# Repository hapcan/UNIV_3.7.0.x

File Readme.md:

UNIV 3.7.0.x
============

BlIND CONTROLLER - 3 channel for AC motors 230V 200VA for DIN rail

Device webpage: http://hapcan.com/devices/universal/univ_3/univ_3-7-0-x/

Hardware created in Eagle PCB Software http://www.cadsoftusa.com/

Firmware created in Microchip MPLAB http://www.microchip.com/mplabide/ in assembly language

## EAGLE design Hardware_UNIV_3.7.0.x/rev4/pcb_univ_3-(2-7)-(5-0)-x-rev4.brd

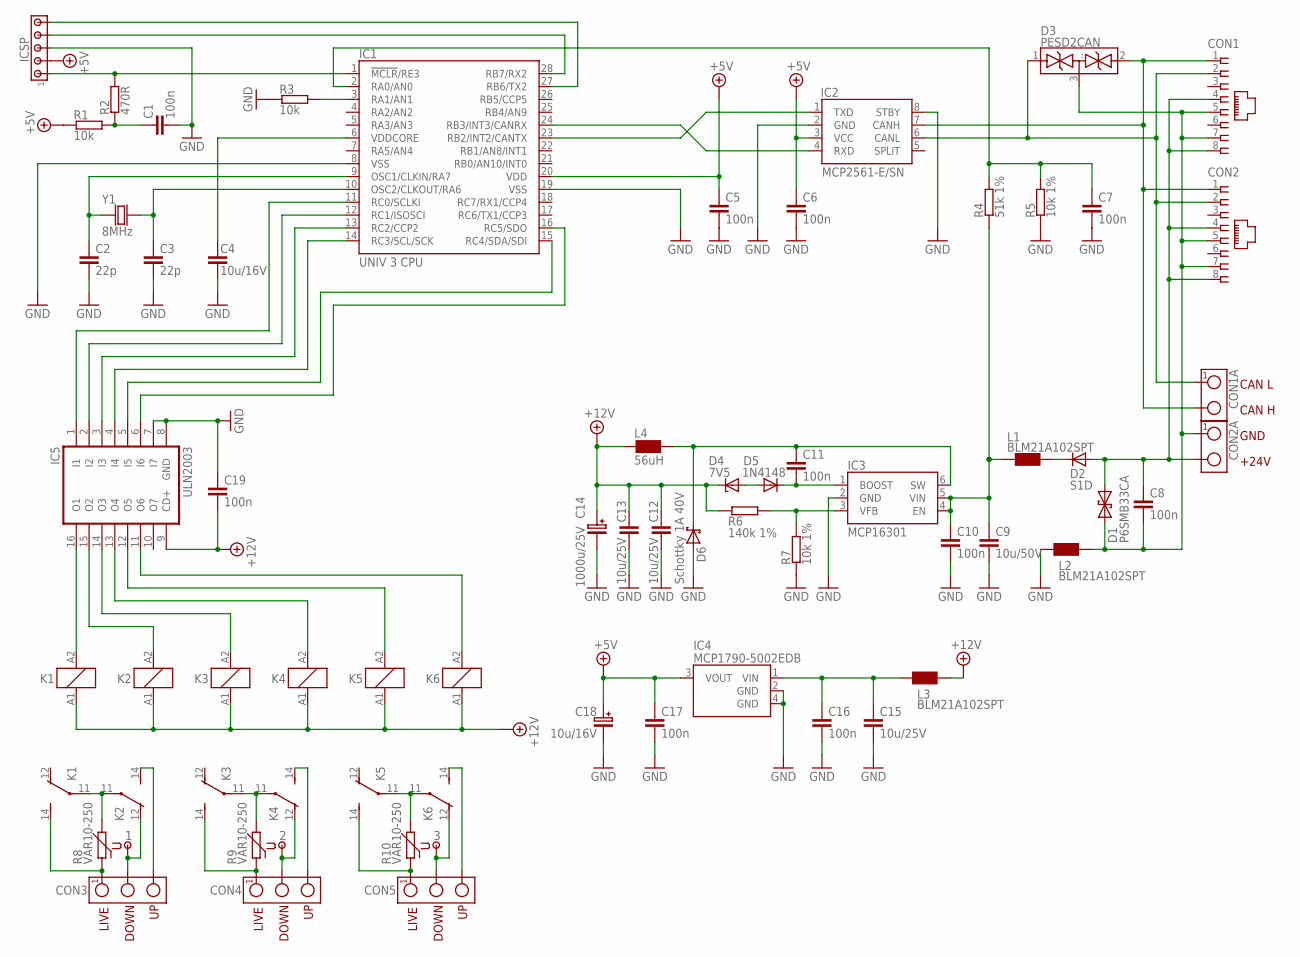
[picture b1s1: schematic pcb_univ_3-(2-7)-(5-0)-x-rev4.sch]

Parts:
1, 2, 3: HEADER11X0.9; SIP-1
C1, C5, C6, C7, C8, C10, C11, C16, C17, C19: 100n; 0805
C2, C3: 22p; 0805
C4: 10u/16V; 0805
C9: 10u/50V; 1210
C12, C13, C15: 10u/25V; 1206
C14: 1000u/25V; CAP-5X10.5
C18: 10u/16V; SMC_B
CON1, CON2: RJ45-SOCKET; RJ45-PCB-SOCKET
CON1A, CON2A: TERMINAL-2; ARK2-5X10,5MM
CON3, CON4, CON5: TERMINAL-3-5X10.5MM; ARK3-5X10.5MM
D1: P6SMB33CA; DO-214_TRANSIL2
D2: S1D; DO-214
D3: PESD2CAN; SOT-23
D4: 7V5; SOD-80
D5: 1N4148; 0805
D6: Schottky 1A 40V; DO-214
IC1: UNIV 3 CPU; UNIV3CPU
IC2: MCP2561-E/SN; SO-08
IC3: MCP16301; SOT-23-6
IC4: MCP1790-5002EDB; SOT-223
IC5: ULN2003; SO-16
ICSP: HEADER5; SIP-5
K1, K2, K3, K4, K5, K6: RELAY_SNR_SPDTV; RELAY_SNR_SPDT_V
L1, L2, L3: BLM21A102SPT; 0805
L4: 56uH; CHOKE-DER0705
R1, R3: 10k; 0805
R2: 470R; 0805
R4: 51k 1%; 0805
R5, R7: 10k 1%; 0805
R6: 140k 1%; 0805
R8, R9, R10: VAR10-250; VARISTOR1
Y1: 8MHz; CRYSTAL-HC49V

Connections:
+5V: C5.1, C6.1, C17.1, C18.+ (1), IC1.20 (VDD), IC2.3 (VCC), IC4.3 (VOUT), ICSP.2, R1.1
+12V: C12.1, C13.1, C14.+ (1), C19.2, D4.C, IC5.9 (CD+), K1.A1 (1), K2.A1 (1), K3.A1 (1), K4.A1 (1), K5.A1 (1), K6.A1 (1), L3.2, L4.1, R6.1
GND: C1.2, C2.2, C3.2, C4.2, C5.2, C6.2, C7.2, C9.2, C10.2, C12.2, C13.2, C14.- (2), C15.2, C16.2, C17.2, C18.- (2), C19.1, D6.A, IC1.8 (VSS), IC1.19 (VSS), IC2.2 (GND), IC2.8 (STBY), IC3.2 (GND), IC4.2 (GND), IC4.4 (GND), IC5.7 (I7), IC5.8 (GND), ICSP.3, L2.1, R3.1, R5.1, R7.1
unnamed: D2.C, L1.2
unnamed: IC1.24 (RB3/INT3/CANRX), IC2.4 (RXD)
unnamed: IC1.23 (RB2/INT2/CANTX), IC2.1 (TXD)
unnamed: CON1.1, CON1A.2, CON2.1, D3.2 (..), IC2.7 (CANH)
unnamed: C9.1, C10.1, IC3.4 (EN), IC3.5 (VIN), L1.1, R4.1
unnamed: C15.1, C16.1, IC4.1 (VIN), L3.1
unnamed: C1.1, R1.2, R2.1
unnamed: IC1.1 (!MCLR!/RE3), ICSP.1, R2.2
unnamed: C8.1, CON1.4, CON1.8, CON2.4, CON2.8, CON2A.2, D1.C (2), D2.A
unnamed: IC1.28 (RB7/RX2), ICSP.4
unnamed: IC1.12 (RC1/ISOSCI), IC5.2 (I2)
unnamed: IC1.3 (RA1/AN1), R3.2
unnamed: C8.2, CON1.5, CON1.7, CON2.5, CON2.7, CON2A.1, D1.A (1), D3.3 (...), L2.2
unnamed: IC1.27 (RB6/TX2), ICSP.5
unnamed: C3.1, IC1.10 (OSC2/CLKOUT/RA6), Y1.2
unnamed: C7.1, IC1.2 (RA0/AN0), R4.2, R5.2
unnamed: C11.1, D6.C, IC3.6 (SW), L4.2
unnamed: IC1.11 (RC0/SCLKI), IC5.1 (I1)
unnamed: IC1.13 (RC2/CCP2), IC5.3 (I3)
unnamed: IC3.3 (VFB), R6.2, R7.2
unnamed: IC5.16 (O1), K1.A2 (2)
unnamed: IC1.14 (RC3/SCL/SCK), IC5.4 (I4)
unnamed: D4.A, D5.2 (A)
unnamed: IC1.15 (RC4/SDA/SDI), IC5.5 (I5)
unnamed: IC5.15 (O2), K2.A2 (2)
unnamed: IC5.14 (O3), K3.A2 (2)
unnamed: CON1.2, CON1A.1, CON2.2, D3.1 (.), IC2.6 (CANL)
unnamed: IC5.13 (O4), K4.A2 (2)
unnamed: IC5.12 (O5), K5.A2 (2)
unnamed: CON3.1, K1.14 (NO), R8.1
unnamed: IC5.11 (O6), K6.A2 (2)
unnamed: K1.11 (COM), K2.11 (COM), R8.2
unnamed: CON3.3, K2.14 (NO)
unnamed: 1.1, CON3.2, K2.12 (NC)
unnamed: K3.11 (COM), K4.11 (COM), R9.2
unnamed: 2.1, CON4.2, K4.12 (NC)
unnamed: C11.2, D5.1 (C), IC3.1 (BOOST)
unnamed: CON4.3, K4.14 (NO)
unnamed: C2.1, IC1.9 (OSC1/CLKIN/RA7), Y1.1
unnamed: 3.1, CON5.2, K6.12 (NC)
unnamed: CON5.3, K6.14 (NO)
unnamed: IC1.16 (RC5/SDO), IC5.6 (I6)
unnamed: K5.11 (COM), K6.11 (COM), R10.2
unnamed: C4.1, IC1.6 (VDDCORE)
unnamed: CON4.1, K3.14 (NO), R9.1
unnamed: CON5.1, K5.14 (NO), R10.1

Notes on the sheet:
CAN L
CAN H
GND
+24V
DOWN
LIVE

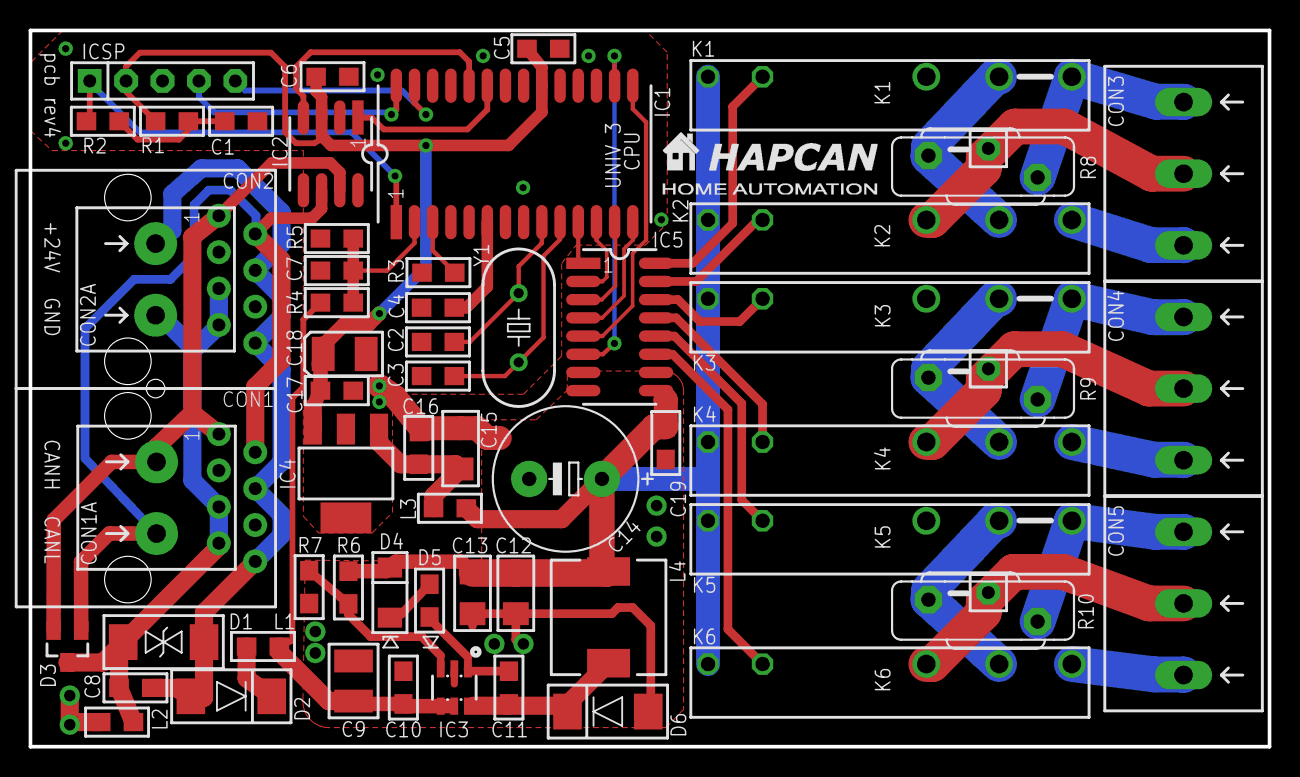
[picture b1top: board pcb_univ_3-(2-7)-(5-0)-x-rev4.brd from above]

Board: 2 copper layers, 86.5 x 50.0 mm, 62 parts (0 on the bottom side), 49 nets.

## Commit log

2014-04-28 hardware revision 1
2014-04-28 firmware UNIV 3.7.0.0-rev0
2015-11-08 firmware UNIV 3.7.0.0 revision 1
2015-12-13 hardware UNIV 3.7.0.x rev1
2015-12-13 Revert "firmware UNIV 3.7.0.0 revision 1"
    This reverts commit 6f1e245d9285862215d36a8d2accf2088a5eb327.
2015-12-13 hardware UNIV 3.7.0.x revision 1
2015-12-13 hardware UNIV 3.7.0.x revision 3
2017-03-05 hardware UNIV 3.7.0.x revision 4
2022-11-05 firmware UNIV 3.7.0.0 revision 2
2022-11-05 MIT license
2024-06-25 hardware UNIV 3.7.0.x revision 4 gerber
